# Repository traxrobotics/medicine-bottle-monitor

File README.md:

# Medication Bottle Monitor (Rev 2 board)

A small, low power board that sits under a medication container and logs when it is handled.
Built around an ESP32 C3 with a Hall effect sensor, an accelerometer and a real time clock.

**Status:** Rev 2 boards received, bring up and testing in progress.

## Hardware features
- ESP32 C3 (WROOM 02) with Wi-Fi and Bluetooth LE
- Native USB, so programming needs no USB to serial chip
- USB C charging with a TP4056 and DW01A battery protection
- Load sharing: runs from USB while the lithium battery charges
- 3.3 V LDO (AP2112K)
- ADXL343 3 axis accelerometer
- DRV5032FA low power Hall sensor
- DS3231 real time clock with CR1220 backup
- 24LC256 EEPROM for storing events
- SSD1306 OLED header
- Deep sleep, with wake from the Hall sensor, accelerometer or clock alarm

## Board
2 layer, about 63 x 54 mm, 3 mounting holes. KiCad 10 project in `hardware/kicad`, Gerbers in `hardware/gerbers`, BOM in `hardware/bom`, schematic in `docs`.

## Flash the logger firmware
1. Install the ESP32 board package in Arduino IDE and pick "ESP32C3 Dev Module".
2. Set "USB CDC On Boot" to Enabled.
3. Hold BOOT, tap RESET, then upload `firmware/logger.ino`.
4. Run `python firmware/logger.py <port>` to save a CSV of accelerometer and Hall sensor readings.

`firmware/logger.ino` has not been tested on hardware yet.

Patent pending.

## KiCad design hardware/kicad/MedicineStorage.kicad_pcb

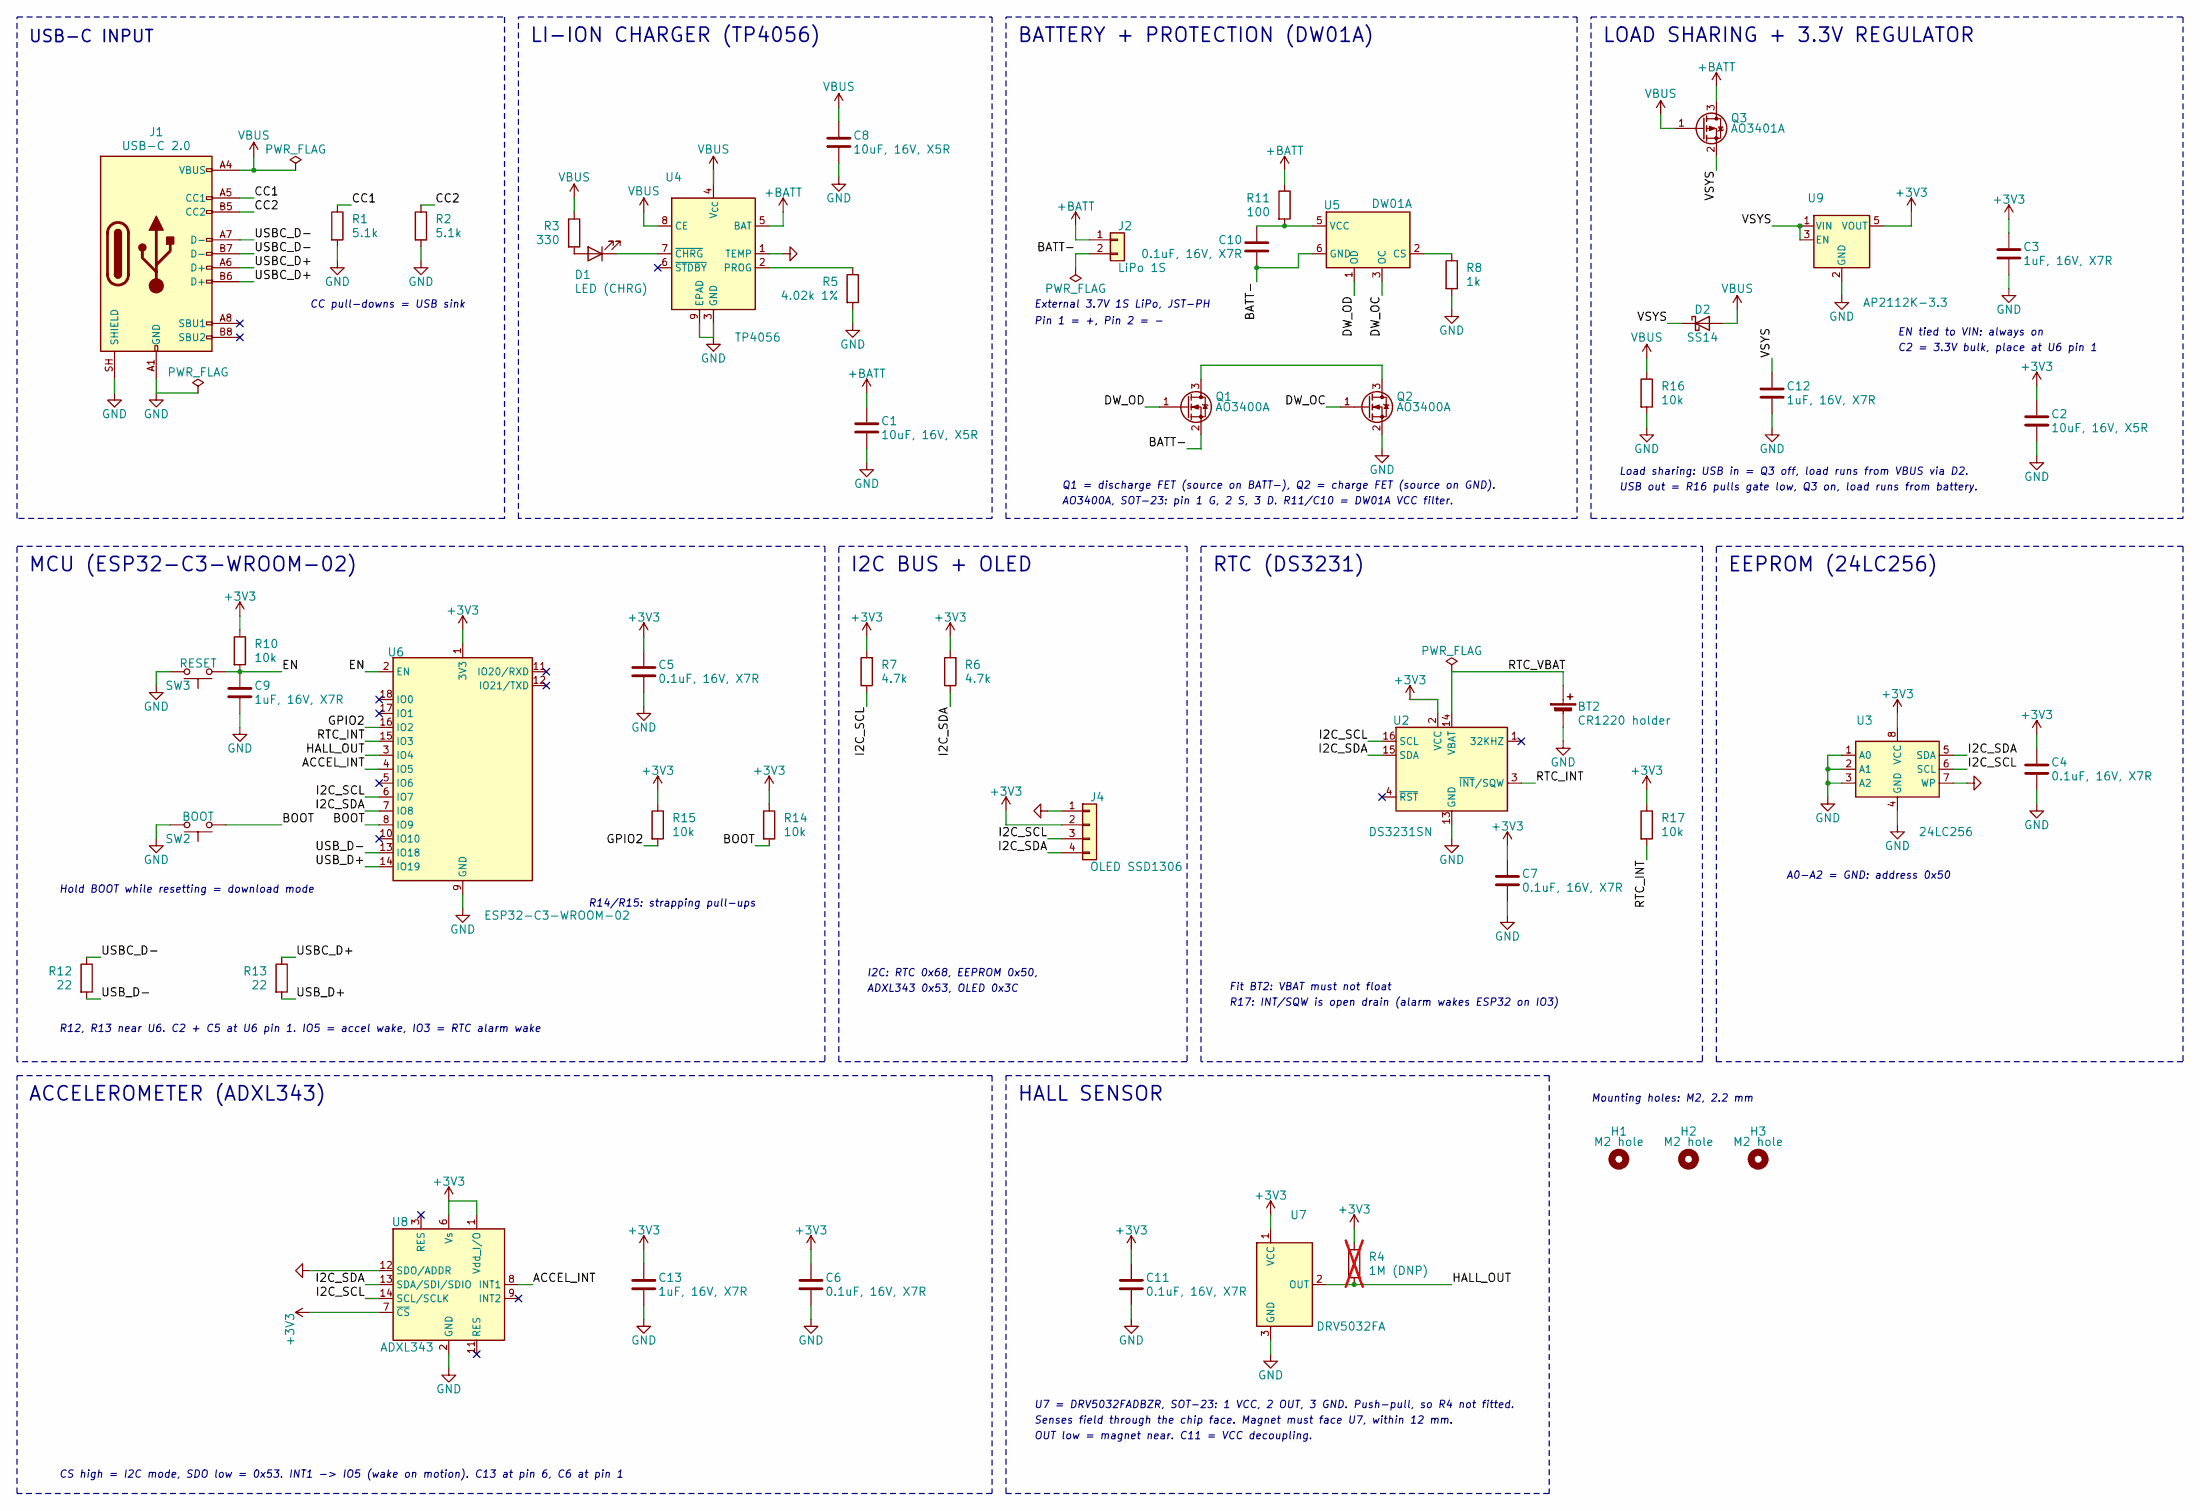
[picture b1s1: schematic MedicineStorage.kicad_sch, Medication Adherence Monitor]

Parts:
BT2: CR1220 holder; BatteryHolder_Keystone_3000_1x12mm; MPN Keystone 3000 (CR1220 holder, SMT) + CR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
C1, C2, C8: 10uF, 16V, X5R; C_0805_2012Metric
C3, C9, C12, C13: 1uF, 16V, X7R; C_0805_2012Metric
C4, C5, C6, C7, C10, C11: 0.1uF, 16V, X7R; C_0805_2012Metric
D1: LED (CHRG); LED_D5.0mm; MPN 5mm LED
D2: SS14; D_SMA; MPN Vishay SS14-E3/61T
H1, H2, H3: M2 hole; MountingHole_2.2mm_M2
J1: USB-C 2.0; USB_C_Receptacle_GCT_USB4085; MPN GCT USB4085-GF-A
J2: LiPo 1S; JST_PH_B2B-PH-K_1x02_P2.00mm_Vertical; MPN JST B2B-PH-K-S(LF)(SN)
J4: OLED SSD1306; PinSocket_1x04_P2.54mm_Vertical; MPN 1x4 2.54mm female header
Q1, Q2: AO3400A; SOT-23; MPN AO3400A
Q3: AO3401A; SOT-23; MPN AO3401A
R1, R2: 5.1k; R_0805_2012Metric
R3: 330; R_0805_2012Metric
R4: 1M (DNP); R_0805_2012Metric; MPN not fitted (1M 0805 only if DRV5032FC i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; not fitted
R5: 4.02k 1%; R_0805_2012Metric; MPN 4.02k 1% 0805
R6, R7: 4.7k; R_0805_2012Metric
R8: 1k; R_0805_2012Metric
R10, R14, R15, R16, R17: 10k; R_0805_2012Metric
R11: 100; R_0805_2012Metric
R12, R13: 22; R_0805_2012Metric
SW2: BOOT; SW_PUSH_6mm_H4.3mm; MPN C&K PTS645SM43-2 LFS
SW3: RESET; SW_PUSH_6mm_H4.3mm; MPN C&K PTS645SM43-2 LFS
U2: DS3231SN; SOIC-16W_7.5x10.3mm_P1.27mm; MPN DS3231SN#
U3: 24LC256; SOIC-8_3.9x4.9mm_P1.27mm; MPN 24LC256-I/SN
U4: TP4056; SOIC-8-1EP_3.9x4.9mm_P1.27mm_EP2.41x3.3mm_ThermalVias; MPN TP4056-42-ESOP8 (NanJing Top Power, LCS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
U5: DW01A; SOT-23-6; MPN DW01A-G (Fortune)
U6: ESP32-C3-WROOM-02; MPN ESP32-C3-WROOM-02-N4
U7: DRV5032FA; SOT-23; MPN DRV5032FADBZR
U8: ADXL343; LGA-14_3x5mm_P0.8mm_LayoutBorder1x6y; MPN ADXL343BCCZ
U9: AP2112K-3.3; SOT-23-5; MPN AP2112K-3.3TRG1

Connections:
+3V3: C2.1, C3.2, C4.1, C5.1, C6.2, C7.1, C11.1, C13.1, J4.2, R4.2, R6.2, R7.2, R10.1, R14.1, R15.1, R17.1, U2.2 (VCC), U3.8 (VCC), U6.1 (3V3), U7.1 (VCC), U8.1 (Vdd_I/O), U8.6 (Vs), U8.7 (~CS), U9.5 (VOUT)
+BATT: C1.2, J2.1, Q3.3 (D), R11.1, U4.5 (BAT)
/ACCEL_INT: U6.4 (IO5), U8.8 (INT1)
/BATT-: C10.2, J2.2, Q1.2 (S), U5.6 (GND)
/BOOT: R14.2, SW2.1, U6.8 (IO9)
/CC1: J1.A5 (CC1), R1.1
/CC2: J1.B5 (CC2), R2.1
/DW_OC: Q2.1 (G), U5.3 (OC)
/DW_OD: Q1.1 (G), U5.1 (OD)
/EN: C9.1, R10.2, SW3.1, U6.2 (EN)
/GPIO2: R15.2, U6.16 (IO2)
/HALL_OUT: R4.1, U6.3 (IO4), U7.2 (OUT)
/I2C_SCL: J4.3, R7.1, U2.16 (SCL), U3.6 (SCL), U6.6 (IO7), U8.14 (SCL/SCLK)
/I2C_SDA: J4.4, R6.1, U2.15 (SDA), U3.5 (SDA), U6.7 (IO8), U8.13 (SDA/SDI/SDIO)
/RTC_INT: R17.2, U2.3 (~INT/SQW), U6.15 (IO3)
/RTC_VBAT: BT2.1 (+), U2.14 (VBAT)
/USBC_D+: J1.A6 (D+), J1.B6 (D+), R13.1
/USBC_D-: J1.A7 (D-), J1.B7 (D-), R12.1
/USB_D+: R13.2, U6.14 (IO19)
/USB_D-: R12.2, U6.13 (IO18)
/VSYS: C12.1, D2.1 (K), Q3.2 (S), U9.1 (VIN), U9.3 (EN)
GND: BT2.2 (-), C1.1, C2.2, C3.1, C4.2, C5.2, C6.1, C7.2, C8.2, C9.2, C11.2, C12.2, C13.2, J1.A1 (GND), J1.A12 (GND), J1.B1 (GND), J1.B12 (GND), J1.SH (SHIELD), J4.1, Q2.2 (S), R1.2, R2.2, R5.2, R8.2, R16.2, SW2.2, SW3.2, U2.5 (GND), U2.6 (GND), U2.7 (GND), U2.8 (GND), U2.9 (GND), U2.10 (GND), U2.11 (GND), U2.12 (GND), U2.13 (GND), U3.1 (A0), U3.2 (A1), U3.3 (A2), U3.4 (GND), U3.7 (WP), U4.1 (TEMP), U4.3 (GND), U4.9 (EPAD), U6.9 (GND), U6.19 (GND), U7.3 (GND), U8.2 (GND), U8.4 (GND), U8.5 (GND), U8.12 (SDO/ADDR), U9.2 (GND)
unnamed: D1.2 (A), R3.2
unnamed: D1.1 (K), U4.7 (~CHRG)
unnamed: Q1.3 (D), Q2.3 (D)
unnamed: R5.1, U4.2 (PROG)
unnamed: R8.1, U5.2 (CS)
unnamed: C10.1, R11.2, U5.5 (VCC)
VBUS: C8.1, D2.2 (A), J1.A4 (VBUS), J1.A9 (VBUS), J1.B4 (VBUS), J1.B9 (VBUS), Q3.1 (G), R3.1, R16.1, U4.4 (V_{CC}), U4.8 (CE)

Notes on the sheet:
Q1 = discharge FET (source on BATT-), Q2 = charge FET (source on GND).
USB out = R16 pulls gate low, Q3 on, load runs from battery.
EN tied to VIN: always on
R12, R13 near U6. C2 + C5 at U6 pin 1. IO5 = accel wake, IO3 = RTC alarm wake
External 3.7V 1S LiPo, JST-PH
AO3400A, SOT-23: pin 1 G, 2 S, 3 D. R11/C10 = DW01A VCC filter.
I2C: RTC 0x68, EEPROM 0x50,
LI-ION CHARGER (TP4056)
CC pull-downs = USB sink
CS high = I2C mode, SDO low = 0x53. INT1 -> IO5 (wake on motion). C13 at pin 6, C6 at pin 1
C2 = 3.3V bulk, place at U6 pin 1
RTC (DS3231)
Senses field through the chip face. Magnet must face U7, within 12 mm.
HALL SENSOR
R14/R15: strapping pull-ups
Hold BOOT while resetting = download mode
R17: INT/SQW is open drain (alarm wakes ESP32 on IO3)
Fit BT2: VBAT must not float
EEPROM (24LC256)
LOAD SHARING + 3.3V REGULATOR
MCU (ESP32-C3-WROOM-02)
Load sharing: USB in = Q3 off, load runs from VBUS via D2.
A0-A2 = GND: address 0x50
ACCELEROMETER (ADXL343)
Pin 1 = +, Pin 2 = -
OUT low = magnet near. C11 = VCC decoupling.
USB-C INPUT
I2C BUS + OLED
Mounting holes: M2, 2.2 mm
ADXL343 0x53, OLED 0x3C
U7 = DRV5032FADBZR, SOT-23: 1 VCC, 2 OUT, 3 GND. Push-pull, so R4 not fitted.
BATTERY + PROTECTION (DW01A)

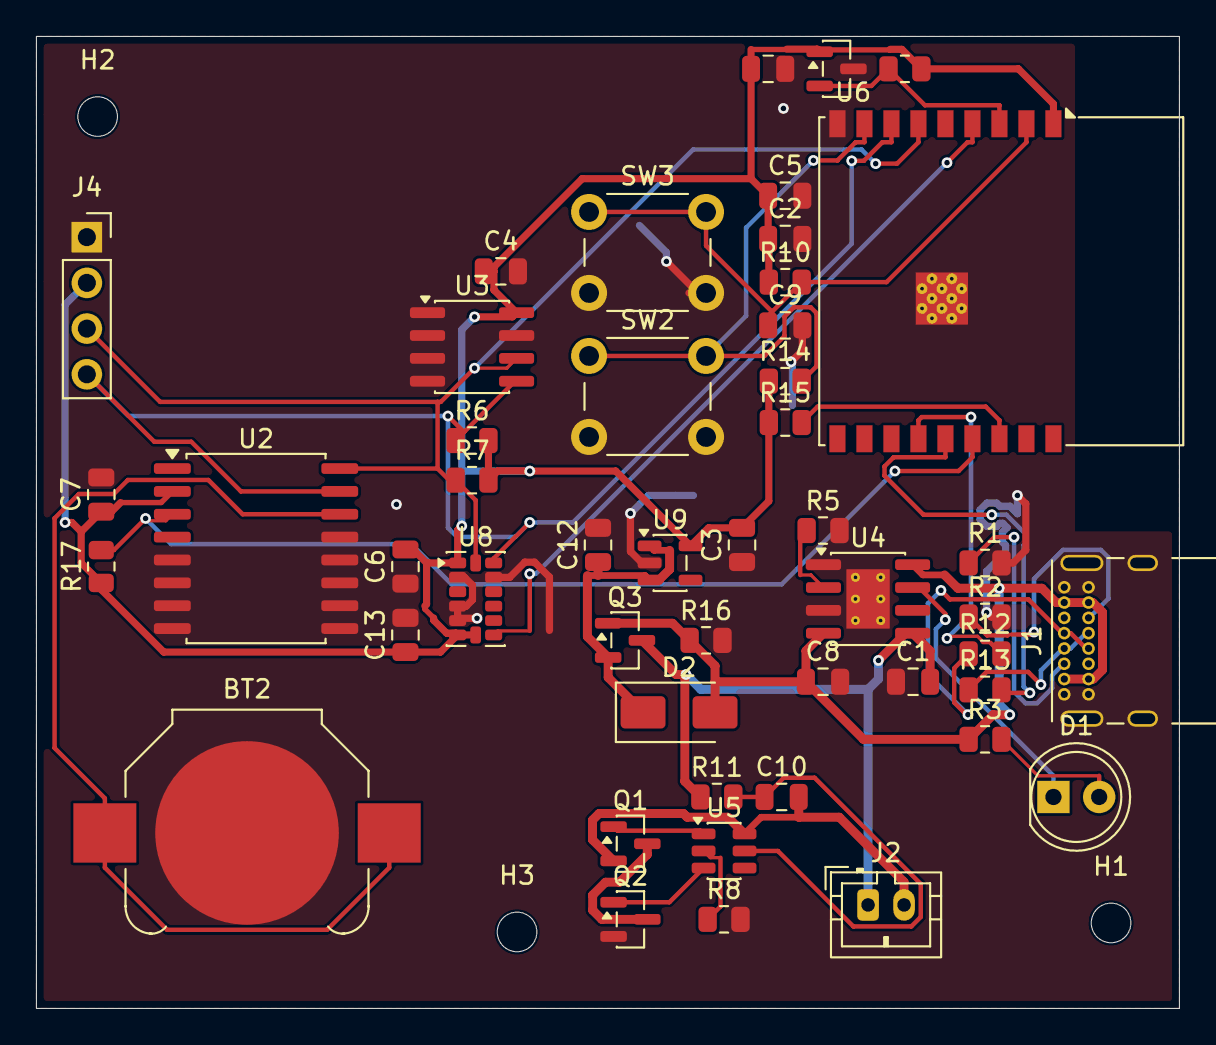
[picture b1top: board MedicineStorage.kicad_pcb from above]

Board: 2 copper layers, 63.5 x 54.0 mm, 51 parts (0 on the bottom side), 29 nets.

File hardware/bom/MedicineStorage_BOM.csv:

"Designator","Qty","Value","Footprint","LCSC","Description","MPN","#","Manufacturer"
"BT2","1","CR1220 holder","Battery:BatteryHolder_Keystone_3000_1x12mm","","Single-cell battery","","1",""
"C1-C2","2","10uF, 16V, X5R","Capacitor_SMD:C_0805_2012Metric","","Unpolarized capacitor","","2",""
"C3","1","1uF, 16V, X7R","Capacitor_SMD:C_0805_2012Metric","","Unpolarized capacitor","","3",""
"C4-C5-C6-C7","4","0.1uF, 16V, X7R","Capacitor_SMD:C_0805_2012Metric","","Unpolarized capacitor","","4",""
"C8","1","10uF, 16V, X5R","Capacitor_SMD:C_0805_2012Metric","","TP4056 VCC input cap","","5",""
"C9","1","1uF, 16V, X7R","Capacitor_SMD:C_0805_2012Metric","","EN RC delay cap","","6",""
"C10","1","0.1uF, 16V, X7R","Capacitor_SMD:C_0805_2012Metric","","DW01A VCC filter cap","","7",""
"C11","1","0.1uF, 16V, X7R","Capacitor_SMD:C_0805_2012Metric","","DRV5032 VCC decoupling","","8",""
"C12","1","1uF, 16V, X7R","Capacitor_SMD:C_0805_2012Metric","","AP2112K input cap on VSYS","","9",""
"C13","1","1uF, 16V, X7R","Capacitor_SMD:C_0805_2012Metric","","ADXL343 VS decoupling (place at pin 6)","","10",""
"D1","1","LED (CHRG)","LED_THT:LED_D5.0mm","","Light emitting diode","","11",""
"D2","1","SS14","Diode_SMD:D_SMA","","Schottky, VBUS to system rail","","12",""
"H1-H2-H3","3","M2 hole","MountingHole:MountingHole_2.2mm_M2","","M2 mounting hole, 2.2 mm","","13",""
"J1","1","USB-C 2.0","Connector_USB:USB_C_Receptacle_GCT_USB4085","","USB 2.0-only 16P Type-C Receptacle connector","","14",""
"J2","1","LiPo 1S","Connector_JST:JST_PH_B2B-PH-K_1x02_P2.00mm_Vertical","","Generic connector, single row, 01x02, script generated (kicad-library-utils/schlib/autogen/connector/)","","15",""
"J4","1","OLED SSD1306","Connector_PinSocket_2.54mm:PinSocket_1x04_P2.54mm_Vertical","","Generic connector, single row, 01x04, script generated (kicad-library-utils/schlib/autogen/connector/)","","16",""
"Q1-Q2","2","AO3400A","Package_TO_SOT_SMD:SOT-23","","30V N-channel MOSFET, logic level","8205A or DMC2400U","17",""
"Q3","1","AO3401A","Package_TO_SOT_SMD:SOT-23","","P-channel MOSFET, load sharing switch","","18",""
"R1-R2","2","5.1k","Resistor_SMD:R_0805_2012Metric","","Resistor","","19",""
"R3","1","330","Resistor_SMD:R_0805_2012Metric","","Resistor","","20",""
"R5","1","4.02k 1%","Resistor_SMD:R_0805_2012Metric","","Resistor","","21",""
"R6-R7","2","4.7k","Resistor_SMD:R_0805_2012Metric","","Resistor","","22",""
"R8","1","1k","Resistor_SMD:R_0805_2012Metric","","Resistor","","23",""
"R10","1","10k","Resistor_SMD:R_0805_2012Metric","","Resistor","","24",""
"R11","1","100","Resistor_SMD:R_0805_2012Metric","","DW01A VCC filter resistor","","25",""
"R12","1","22","Resistor_SMD:R_0805_2012Metric","","USB D- series resistor","","26",""
"R13","1","22","Resistor_SMD:R_0805_2012Metric","","USB D+ series resistor","","27",""
"R14","1","10k","Resistor_SMD:R_0805_2012Metric","","GPIO9 pull-up","","28",""
"R15","1","10k","Resistor_SMD:R_0805_2012Metric","","GPIO2 pull-up","","29",""
"R16","1","10k","Resistor_SMD:R_0805_2012Metric","","Q3 gate pull-down / VBUS discharge","","30",""
"R17","1","10k","Resistor_SMD:R_0805_2012Metric","","DS3231 INT/SQW pull-up (open drain)","","31",""
"SW2","1","BOOT","Button_Switch_THT:SW_PUSH_6mm_H4.3mm","","Push button switch, generic, two pins","","32",""
"SW3","1","RESET","Button_Switch_THT:SW_PUSH_6mm_H4.3mm","","Push button switch, generic, two pins","","33",""
"U2","1","DS3231SN","Package_SO:SOIC-16W_7.5x10.3mm_P1.27mm","","Extremely Accurate I2C-Integrated RTC/TCXO/Crystal SOIC-16","DS3231MZ+","34",""
"U3","1","24LC256","Package_SO:SOIC-8_3.9x4.9mm_P1.27mm","","I2C Serial EEPROM, 256Kb, DIP-8/SOIC-8/TSSOP-8/DFN-8","24LC256-I/SN","35",""
"U4","1","TP4056","Package_SO:SOIC-8-1EP_3.9x4.9mm_P1.27mm_EP2.41x3.3mm_ThermalVias","","1A Standalone Linear Li-ion/LiPo single-cell battery charger, 4.2V ±1% charge voltage, VCC = 4.0..8.0V, SOIC-8 (SOP-8)","TP4056-42-ESOP8-R","36",""
"U5","1","DW01A","Package_TO_SOT_SMD:SOT-23-6","","Overcharge, overcurrent and overdischarge protection IC for single cell lithium-ion/polymer battery","DW01A-G","37",""
"U6","1","ESP32-C3-WROOM-02","RF_Module:ESP32-C3-WROOM-02","","802.11 b/g/n Wi­Fi and Bluetooth 5 module, ESP32­C3 SoC, RISC­V microprocessor, On-board antenna","N4","38",""
"U7","1","DRV5032FA","Package_TO_SOT_SMD:SOT-23","","Omnipolar Hall switch, push-pull, 20 Hz, SOT-23 (DBZ)","DRV5032FCDBZR","39",""
"U8","1","ADXL343","Package_LGA:LGA-14_3x5mm_P0.8mm_LayoutBorder1x6y","","3-Axis MEMS Accelerometer, 2/4/8/16g range, I2C/SPI, LGA-14","ADXL343BCCZ-RL","40",""
"U9","1","AP2112K-3.3","Package_TO_SOT_SMD:SOT-23-5","","600mA low dropout linear regulator, with enable pin, 3.8V-6V input voltage range, 3.3V fixed positive output, SOT-23-5","AP2112K-3.3TRG1","41",""
